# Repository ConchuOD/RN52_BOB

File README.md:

## Breakout for the RN52 module.

Essentially works the same as the Adafruit one, with a slightly different pinout. Firstly it was cheaper to do it this way w/ OSHPark as the printer and buying the module from Farnell & secondly it was the first board I made so a good way to practice using Eagle for something simple.

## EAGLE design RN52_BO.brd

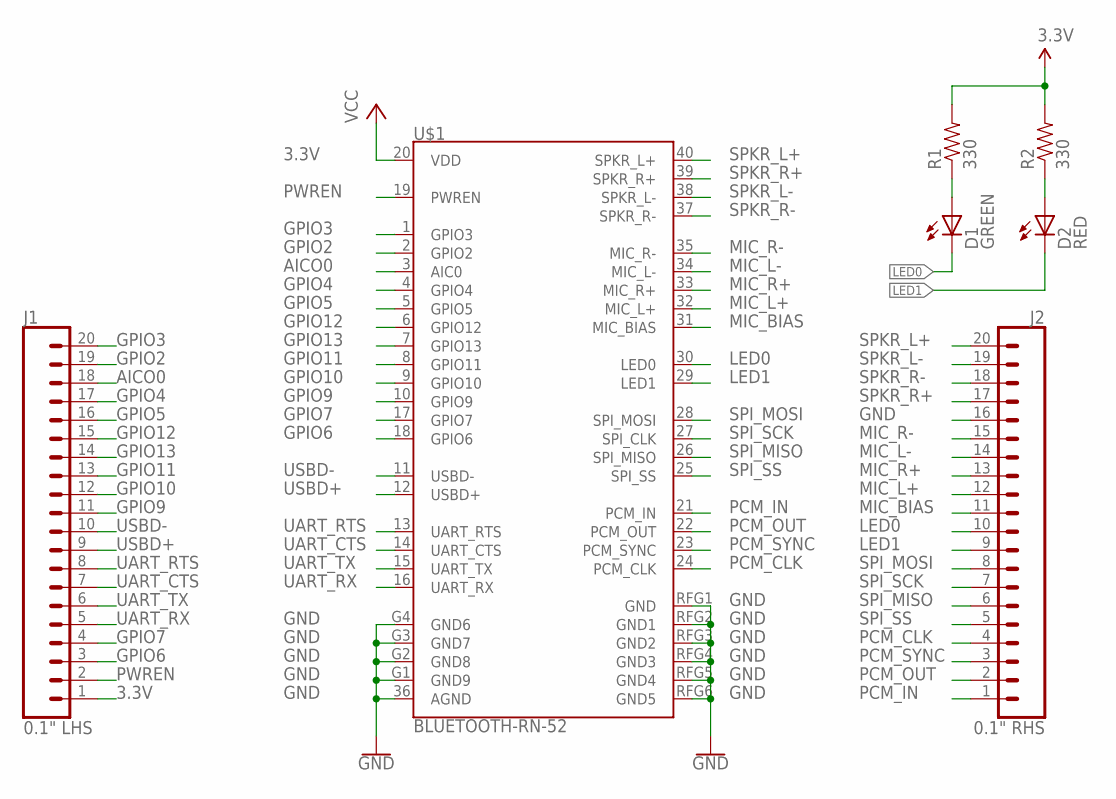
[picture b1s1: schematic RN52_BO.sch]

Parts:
D1: GREEN; LED-0603
D2: RED; LED-0603
J1: 0.1" LHS; 1X20
J2: 0.1" RHS; 1X20
R1, R2: 330; 0603-RES
U$1: BLUETOOTH-RN-52; RN-52

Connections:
3.3V: J1.1, R1.2, R2.2, U$1.20 (VDD)
AICO0: J1.18, U$1.3 (AIC0)
GND: J2.16, U$1.36 (AGND), U$1.G1 (GND9), U$1.G2 (GND8), U$1.G3 (GND7), U$1.G4 (GND6), U$1.RFG1 (GND), U$1.RFG2 (GND1), U$1.RFG3 (GND2), U$1.RFG4 (GND3), U$1.RFG5 (GND4), U$1.RFG6 (GND5)
GPIO2: J1.19, U$1.2 (GPIO2)
GPIO3: J1.20, U$1.1 (GPIO3)
GPIO4: J1.17, U$1.4 (GPIO4)
GPIO5: J1.16, U$1.5 (GPIO5)
GPIO6: J1.3, U$1.18 (GPIO6)
GPIO7: J1.4, U$1.17 (GPIO7)
GPIO9: J1.11, U$1.10 (GPIO9)
GPIO10: J1.12, U$1.9 (GPIO10)
GPIO11: J1.13, U$1.8 (GPIO11)
GPIO12: J1.15, U$1.6 (GPIO12)
GPIO13: J1.14, U$1.7 (GPIO13)
LED0: D1.C, J2.10, U$1.30 (LED0)
LED1: D2.C, J2.9, U$1.29 (LED1)
MIC_BIAS: J2.11, U$1.31 (MIC_BIAS)
MIC_L+: J2.12, U$1.32 (MIC_L+)
MIC_L-: J2.14, U$1.34 (MIC_L-)
MIC_R+: J2.13, U$1.33 (MIC_R+)
MIC_R-: J2.15, U$1.35 (MIC_R-)
unnamed: D2.A, R2.1
unnamed: D1.A, R1.1
PCM_CLK: J2.4, U$1.24 (PCM_CLK)
PCM_IN: J2.1, U$1.21 (PCM_IN)
PCM_OUT: J2.2, U$1.22 (PCM_OUT)
PCM_SYNC: J2.3, U$1.23 (PCM_SYNC)
PWREN: J1.2, U$1.19 (PWREN)
SPI_MISO: J2.6, U$1.26 (SPI_MISO)
SPI_MOSI: J2.8, U$1.28 (SPI_MOSI)
SPI_SCK: J2.7, U$1.27 (SPI_CLK)
SPI_SS: J2.5, U$1.25 (SPI_SS)
SPKR_L+: J2.20, U$1.40 (SPKR_L+)
SPKR_L-: J2.19, U$1.38 (SPKR_L-)
SPKR_R+: J2.17, U$1.39 (SPKR_R+)
SPKR_R-: J2.18, U$1.37 (SPKR_R-)
UART_CTS: J1.7, U$1.14 (UART_CTS)
UART_RTS: J1.8, U$1.13 (UART_RTS)
UART_RX: J1.5, U$1.16 (UART_RX)
UART_TX: J1.6, U$1.15 (UART_TX)
USBD+: J1.9, U$1.12 (USBD+)
USBD-: J1.10, U$1.11 (USBD-)

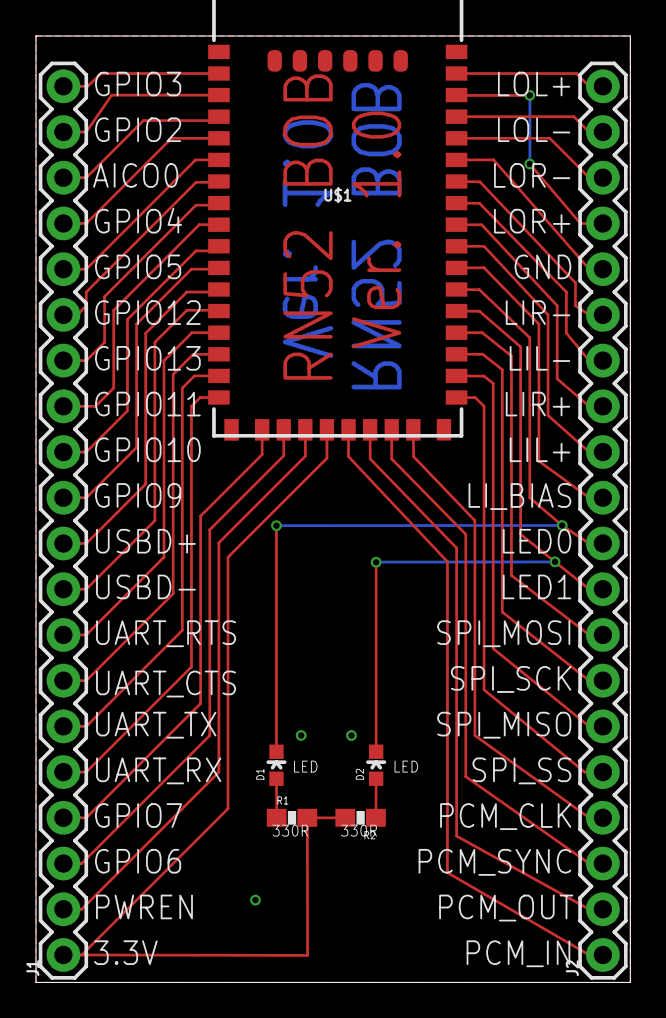
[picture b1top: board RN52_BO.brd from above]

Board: 2 copper layers, 33.0 x 52.6 mm, 7 parts (0 on the bottom side), 42 nets.

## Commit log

2018-03-29 ReadMe update.
2018-03-30 Adding HW files
2019-12-10 Making use of eagle redundant - I no longer use it myself
2022-05-22 Create LICENSE

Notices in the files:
parts and their libraries:
SparkFun-RF: Licensing: Creative Commons ShareAlike 4.0 International - https://creativecommons.org/licenses/by-sa/4.0
SparkFun-LED: Licensing: CC v3.0 Share-Alike You are welcome to use this library for commercial purposes.
